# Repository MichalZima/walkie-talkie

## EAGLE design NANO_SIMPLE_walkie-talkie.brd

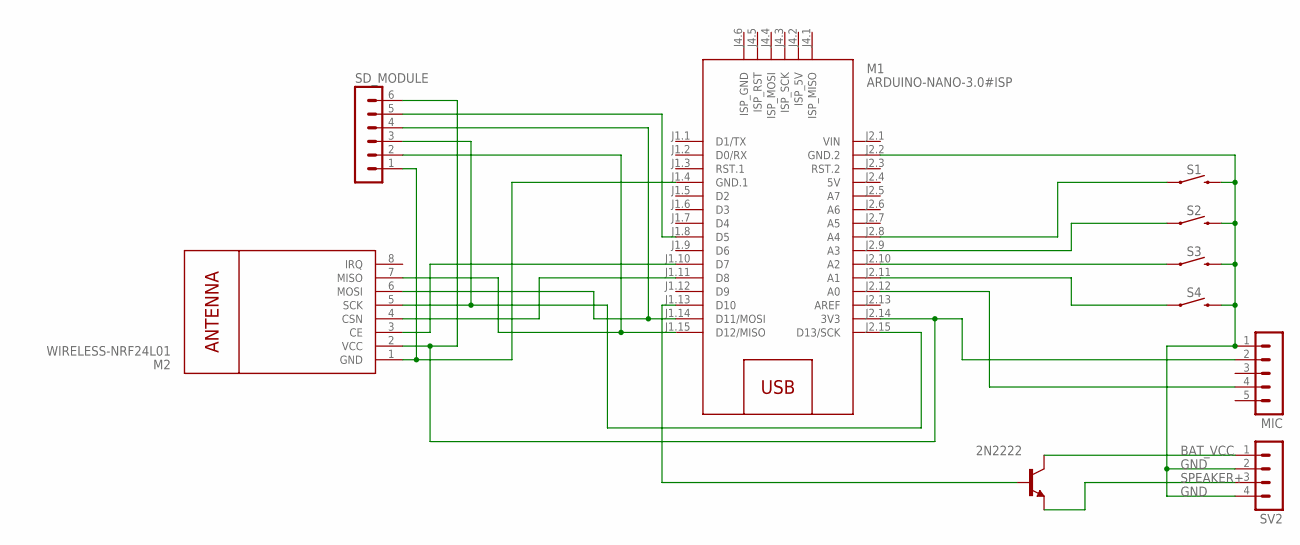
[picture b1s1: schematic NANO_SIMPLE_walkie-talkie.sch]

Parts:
M1: ARDUINO-NANO-3.0#ISP
M2: WIRELESS-NRF24L01
MIC: MA05-1
S1, S2, S3, S4: MOMENTARY-SWITCH-SPST-PTH-6.0MM; TACTILE_SWITCH_PTH_6.0MM
SD_MODULE: MA06-1
SV2: MA04-1
T1: 2N2222; TO18

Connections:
5V: M1.J2.4 (5V)
6: M1.J2.14 (3V3), M2.2 (VCC), MIC.2, SD_MODULE.6
BAT_VCC: SV2.1, T1.3 (C)
GND: M1.J2.2 (GND.2), MIC.1, S1.3 (2), S2.3 (2), S3.3 (2), S4.3 (2), SV2.2, SV2.4
unnamed: M1.J1.8 (D5), SD_MODULE.5
unnamed: M1.J1.4 (GND.1), M2.1 (GND), SD_MODULE.1
unnamed: M1.J1.10 (D7), M2.3 (CE)
unnamed: M1.J1.11 (D8), M2.4 (CSN)
unnamed: M1.J2.15 (D13/SCK), M2.5 (SCK), SD_MODULE.3
unnamed: M1.J1.14 (D11/MOSI), M2.6 (MOSI), SD_MODULE.4
unnamed: M1.J1.15 (D12/MISO), M2.7 (MISO), SD_MODULE.2
unnamed: M1.J2.11 (A1), S4.1
unnamed: M1.J2.10 (A2), S3.1
unnamed: M1.J2.9 (A3), S2.1
unnamed: M1.J2.8 (A4), S1.1
unnamed: M1.J1.13 (D10), T1.2 (B)
unnamed: M1.J2.12 (A0), MIC.4
SPEAKER+: SV2.3, T1.1 (E)
VIN: M1.J2.1 (VIN)

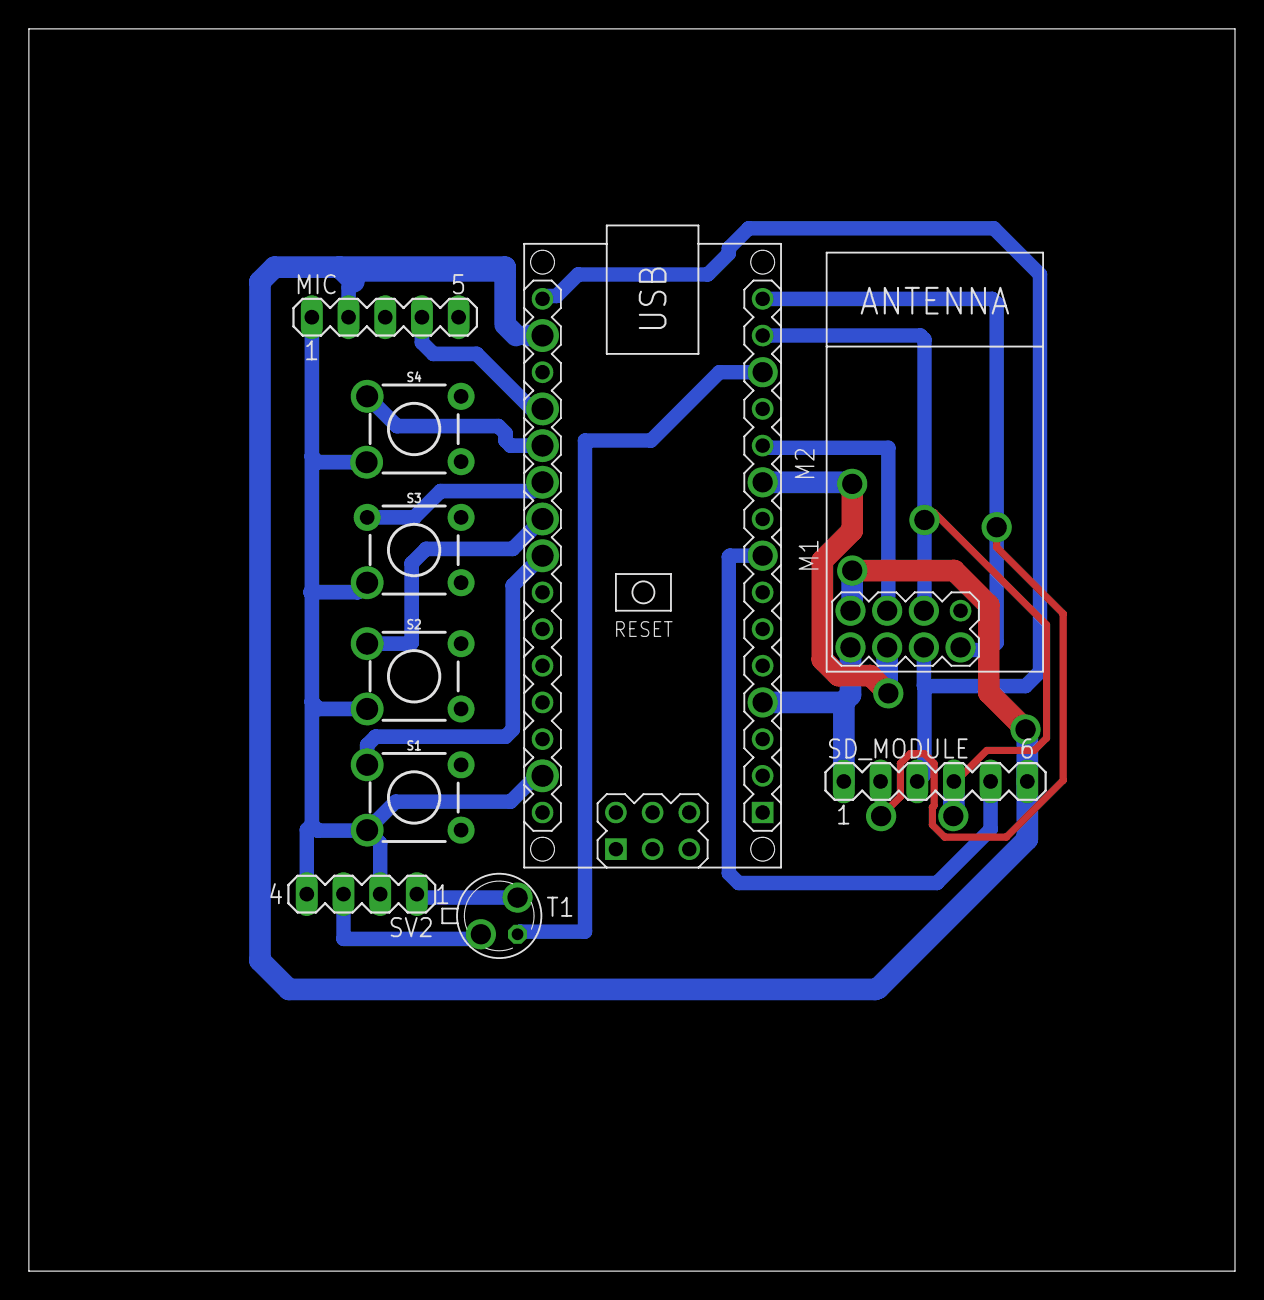
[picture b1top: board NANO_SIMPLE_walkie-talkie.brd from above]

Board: 2 copper layers, 83.5 x 86.0 mm, 10 parts (0 on the bottom side), 17 nets.

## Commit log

2021-06-26 test code for nrf connection
2021-06-26 PCB for manufacturing
2021-06-26 PCB for homemade print

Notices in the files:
parts and their libraries:
diy-modules: Released under the Creative Commons Attribution 4.0 International License: http://creativecommons.org/licenses/by/4.0
SparkFun-Switches: Licensing: Creative Commons ShareAlike 4.0 International - https://creativecommons.org/licenses/by-sa/4.0
